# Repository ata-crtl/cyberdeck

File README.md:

# cyberpad

this is a macro pad inspired by the cyber truck . it has 4 keys , a rotary encoder with a 3d printed knob and a small oled screen . it runs on a xiao rp2040

## what it does

right now the keys are just w a s d , the knob changes the volume and if you press the knob it mutes . the oled shows the name and what the keys do

the firmware is kmk so you dont have to compile anything , you just edit main.py and save it

## pictures

## key layout

    W  A     knob
    S  D     oled

## parts

- 1 xiao rp2040
- 4 mx switches
- 4 1u keycaps
- 1 ec11 rotary encoder (the one with the push button)
- 1 0.91 inch oled , 128x32 , i2c , ssd1306
- 5 1n4148 diodes , through hole
- 1 pcb
- 1 3d printed case
- 1 3d printed knob
- 3 m3 screws

theres also a BOM.csv from kicad if you want it

## pins

| xiao pin | goes to |
|---|---|
| D0 | col 1 (SW1 , SW4) |
| D1 | col 0 (SW2 , SW3) |
| D2 | row 1 |
| D3 | row 0 |
| D4 | oled SDA |
| D5 | oled SCL |
| D7 | encoder B |
| D8 | encoder A |
| D9 | encoder button |
| 3V3 | oled VCC |
| GND | oled and encoder GND |

the encoder button is part of the key matrix , it goes through D5 to row 0

my build log and timelapses are in [journal.md](journal.md)

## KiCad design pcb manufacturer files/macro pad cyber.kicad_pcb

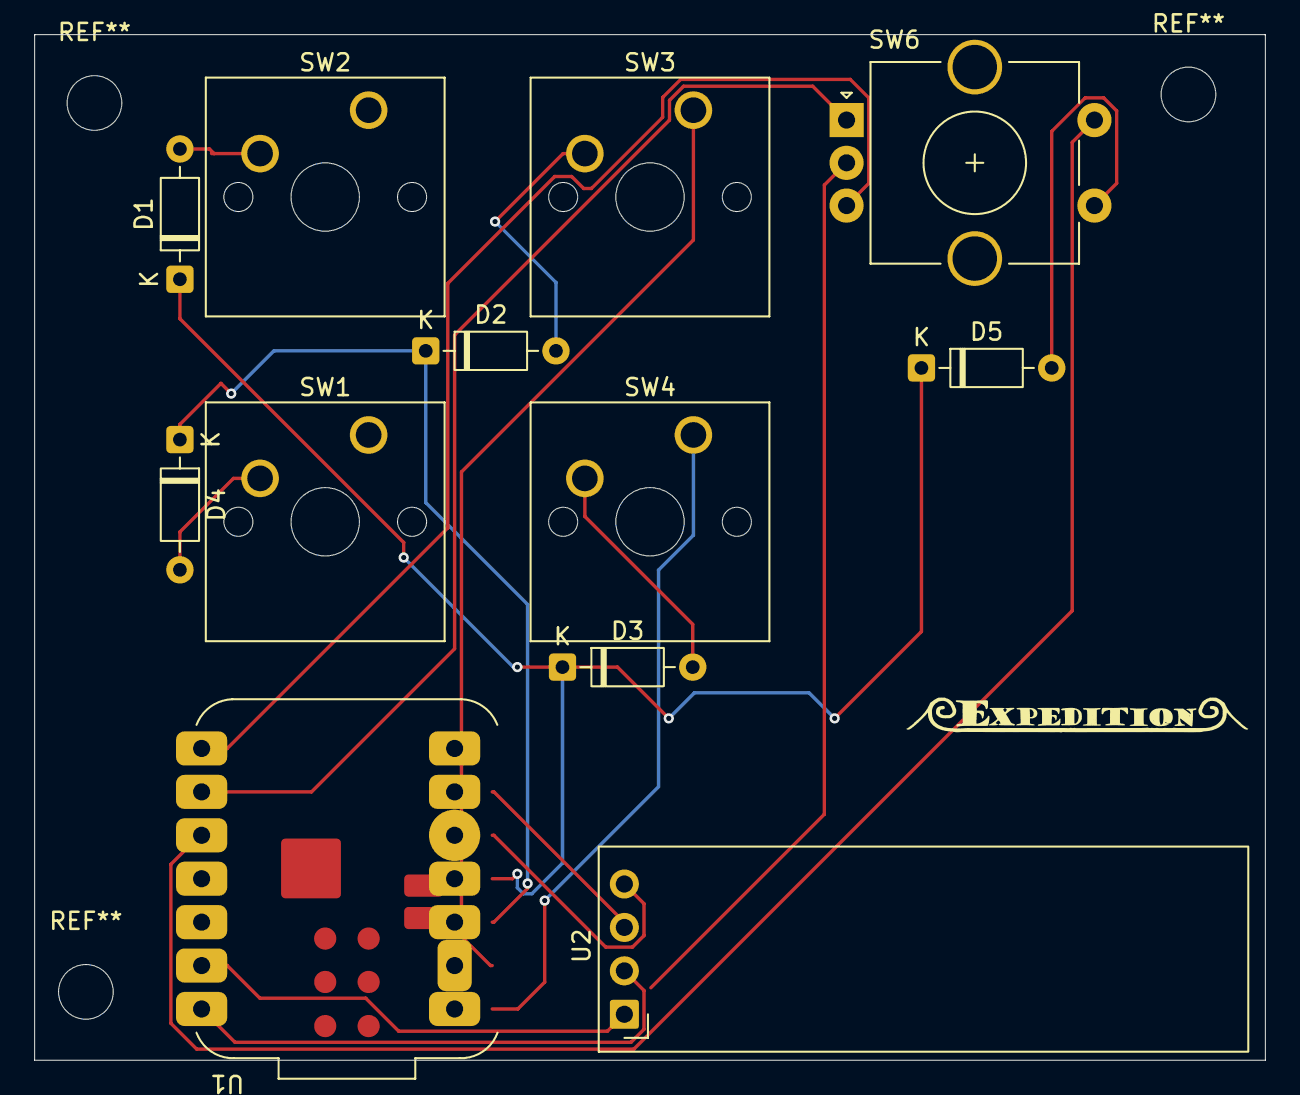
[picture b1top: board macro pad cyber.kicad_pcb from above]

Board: 2 copper layers, 72.0 x 60.0 mm, 12 parts (0 on the bottom side), 16 nets.

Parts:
D1, D2, D3, D4, D5: D; D_DO-35_SOD27_P7.62mm_Horizontal
SW1, SW2, SW3, SW4: SW_Push; SW_Cherry_MX_1.00u_PCB
SW6: RotaryEncoder_Switch; RotaryEncoder_Alps_EC11E-Switch_Vertical_H20mm_CircularMoun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
U1: MOUDLE-SEEEDUINO-XIAO; MCU_Seeed_ESP32C3
U2: ER_OLEDM0.91_1x-I2C

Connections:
/EC11A: SW6.A, U1.9 (PA7_A8_D8_SCK_9)
/EC11B: SW6.B, U1.8 (PB09_A7_D7_RX_8)
/EC11SWB: SW6.S2, U1.10 (PA5_A9_D9_MISO_10)
/ECLLSWA: D5.2 (A), SW6.S1
/SCL: U1.6 (PA9_A5_D5_SCL_6), U2.3 (SCL)
/SDA: U1.5 (PA8_A4_D4_SDA_5), U2.4 (SDA)
/col 0: SW3.1, U1.2 (PA4_A1_D1_2)
/col 1: SW4.1, U1.1 (PA02_A0_D0_1)
/row 0: D1.1 (K), D3.1 (K), D5.1 (K), U1.4 (PA11_A3_D3_4)
/row 1: D2.1 (K), D4.1 (K), U1.-6.3 (PA10_A2_D2_3)
GND: SW6.C, U1.13 (GND_13), U2.1 (GND)
unnamed: D1.2 (A), SW2.2 (2_2)
unnamed: D2.2 (A), SW3.2
unnamed: D3.2 (A), SW4.2
unnamed: D4.2 (A), SW1.2 (2_2)
VCC: U1.14 (5V_14), U2.2 (VCC)

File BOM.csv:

Id,Designator,Footprint,Quantity,Designation
1,D1 D2 D3 D4 D5,D_DO-35_SOD27_P7.62mm_Horizontal,5,D
2,SW1 SW2 SW3 SW4,SW_Cherry_MX_1.00u_PCB,4,SW_Push
3,SW6,RotaryEncoder_Alps_EC11E-Switch_Vertical_H20mm_CircularMountingHoles,1,RotaryEncoder_Switch
4,U1,MCU_Seeed_ESP32C3,1,MOUDLE-SEEEDUINO-XIAO
5,U2,ER_OLEDM0.91_1x-I2C,1,ER_OLEDM0.91_1x-I2C
6,N/A,The 3d printed case and knob,1,N/A
